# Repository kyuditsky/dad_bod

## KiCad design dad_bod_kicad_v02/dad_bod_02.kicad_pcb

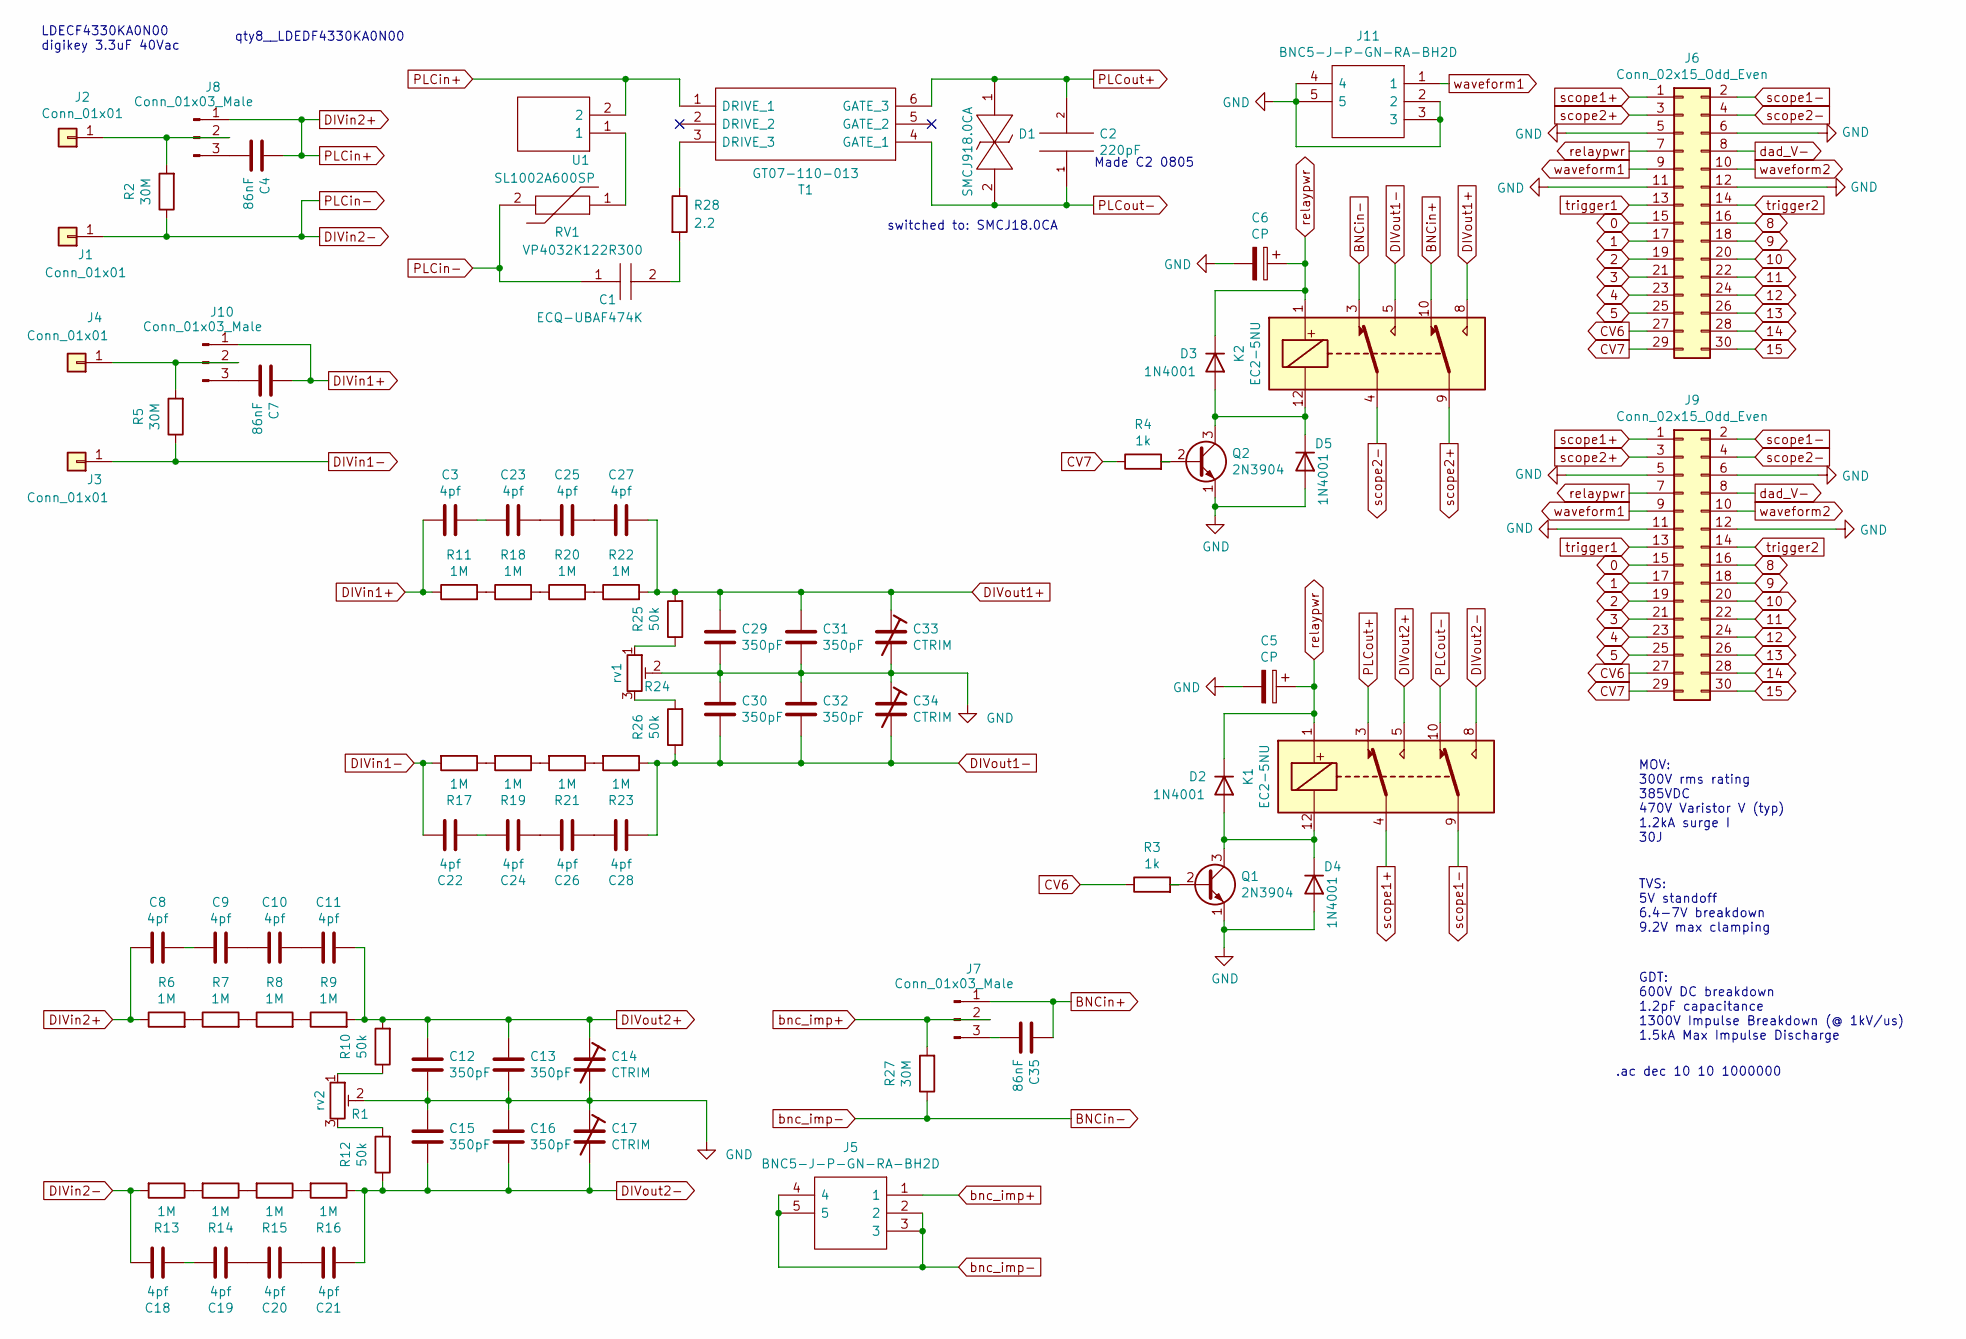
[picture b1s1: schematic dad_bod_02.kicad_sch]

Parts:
C1: ECQ-UBAF474K; ECQ-UBAF474K-3_side; Mouser Part Number 667-ECQ-UBAF474K
C2: 220pF; C_0603_1608Metric_Pad1.08x0.95mm_HandSolder
C3, C8, C9, C10, C11, C18, C19, C20, C21, C22, C23, C24, C25, C26, C27, C28: 4pf; C_0603_1608Metric_Pad1.08x0.95mm_HandSolder
C4, C7, C35: 86nF; C_0603_1608Metric_Pad1.08x0.95mm_HandSolder
C5, C6: CP; EEE1AA220WR
C12, C13, C15, C16, C29, C30, C31, C32: 350pF; C_0603_1608Metric_Pad1.08x0.95mm_HandSolder
C14, C17, C33, C34: CTRIM; C_Trimmer_Voltronics_JQ
D1: SMCJ918.0CA; DIONM7959X262N; Mouser Part Number 576-SMCJ9.0CA
D2, D3, D4, D5: 1N4001; D_DO-41_SOD81_P2.54mm_Vertical_KathodeUp
J1, J2, J3, J4: Conn_01x01; Banana_Jack_S_RA_73099
J5, J11: BNC5-J-P-GN-RA-BH2D; BNC5JPGNRABH2D; Mouser Part Number 200-BNC5JPGNRABH2D
J6: Conn_02x15_Odd_Even; PinHeader_2x15_P2.54mm_Horizontal
J7, J8, J10: Conn_01x03_Male; PinHeader_1x03_P2.54mm_Vertical
J9: Conn_02x15_Odd_Even
K1, K2: EC2-5NU; Relay_DPDT_Kemet_EC2
Q1, Q2: 2N3904; TO-92_Inline
R1: rv2; Potentiometer_Bourns_3314J_Vertical
R2, R5, R27: 30M; R_0603_1608Metric_Pad0.98x0.95mm_HandSolder
R3, R4: 1k; R_0603_1608Metric_Pad0.98x0.95mm_HandSolder
R6, R7, R8, R9, R11, R13, R14, R15, R16, R17, R18, R19, R20, R21, R22, R23: 1M; R_0603_1608Metric_Pad0.98x0.95mm_HandSolder
R10, R12, R25, R26: 50k; R_0603_1608Metric_Pad0.98x0.95mm_HandSolder
R24: rv1; Potentiometer_Bourns_3314J_Vertical
R28: 2.2; R_2010_5025Metric_Pad1.40x2.65mm_HandSolder
RV1: VP4032K122R300; CAPPM10080X500N; Mouser Part Number 80-VP4032K122R300
T1: GT07-110-013; GT07110013; Mouser Part Number 911-GT07-110-013
U1: SL1002A600SP; Mouser Part Number 576-SL1002A600SP

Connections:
0: J6.15, J9.15
1: J6.17, J9.17
2: J6.19, J9.19
3: J6.21, J9.21
4: J6.23, J9.23
5: J6.25, J9.25
8: J6.16, J9.16
9: J6.18, J9.18
10: J6.20, J9.20
11: J6.22, J9.22
12: J6.24, J9.24
13: J6.26, J9.26
14: J6.28, J9.28
15: J6.30, J9.30
BNCin+: C35.2, J7.1, K2.10
BNCin-: J5.2, J5.3, J5.4, J5.5, K2.3, R27.1
CV6: J6.27, J9.27, R3.1
CV7: J6.29, J9.29, R4.1
DIVin1+: C3.2, C7.2, J10.1, R11.1
DIVin1-: C22.1, J3.1, R5.1, R17.2
DIVin2+: C4.2, C8.2, J8.1, R6.1, T1.1 (DRIVE_1), U1.2
DIVin2-: C1.1, C18.1, J1.1, R2.1, R13.2, RV1.2
DIVout1+: C27.1, C29.2, C31.2, C33.1, K2.8, R22.2, R25.2
DIVout1-: C28.2, C30.1, C32.1, C34.2, K2.5, R23.1, R26.1
DIVout2+: C11.1, C12.2, C13.2, C14.1, K1.5, R9.2, R10.2
DIVout2-: C15.1, C16.1, C17.2, C21.2, K1.8, R12.1, R16.1
GND: C5.2, C6.2, C12.1, C13.1, C14.2, C15.2, C16.2, C17.1, C29.1, C30.2, C31.1, C32.2, C33.2, C34.1, D4.2 (A), D5.2 (A), J6.5, J6.6, J6.11, J6.12, J9.5, J9.6, J9.11, J9.12, J11.2, J11.3, J11.4, J11.5, Q1.1 (E), Q2.1 (E), R1.2, R24.2
unnamed: C1.2, R28.2
unnamed: C4.1, J8.3
unnamed: C7.1, J10.3
unnamed: C8.1, C9.2
unnamed: C10.1, C11.2
unnamed: C9.1, C10.2
unnamed: C18.2, C19.1
unnamed: C19.2, C20.1
unnamed: C20.2, C21.1
unnamed: C22.2, C24.1
unnamed: C23.1, C25.2
unnamed: C3.1, C23.2
unnamed: C24.2, C26.1
unnamed: C25.1, C27.2
unnamed: C26.2, C28.1
unnamed: C35.1, J7.3
unnamed: D2.2 (A), D4.1 (K), K1.12, Q1.3 (C)
unnamed: D3.2 (A), D5.1 (K), K2.12, Q2.3 (C)
unnamed: J2.1, J8.2, R2.2
unnamed: J4.1, J10.2, R5.2
unnamed: Q1.2 (B), R3.2
unnamed: Q2.2 (B), R4.2
unnamed: R1.1, R10.1
unnamed: R1.3, R12.2
unnamed: R6.2, R7.1
unnamed: R7.2, R8.1
unnamed: R8.2, R9.1
unnamed: R11.2, R18.1
unnamed: R13.1, R14.2
unnamed: R14.1, R15.2
unnamed: R15.1, R16.2
unnamed: R17.1, R19.2
unnamed: R18.2, R20.1
unnamed: R19.1, R21.2
unnamed: R20.2, R22.1
unnamed: R21.1, R23.2
unnamed: R24.1, R25.1
unnamed: R24.3, R26.2
unnamed: R28.1, T1.3 (DRIVE_3)
unnamed: RV1.1, U1.1
PLCout+: C2.2, D1.1, K1.3, T1.6 (GATE_3)
PLCout-: C2.1, D1.2, K1.10, T1.4 (GATE_1)
bnc_imp+: J5.1, J7.2, R27.2
dad_V-: J6.8, J9.8
relaypwr: C5.1, C6.1, D2.1 (K), D3.1 (K), J6.7, J9.7, K1.1, K2.1
scope1+: J6.1, J9.1, K1.4
scope1-: J6.2, J9.2, K1.9
scope2+: J6.3, J9.3, K2.9
scope2-: J6.4, J9.4, K2.4
trigger1: J6.13, J9.13
trigger2: J6.14, J9.14
waveform1: J6.9, J9.9, J11.1
waveform2: J6.10, J9.10

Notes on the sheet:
LDECF4330KA0N00 digikey 3.3uF 40Vac
Made C2 0805
TVS: 5V standoff 6.4-7V breakdown 9.2V max clamping
GDT: 600V DC breakdown 1.2pF capacitance 1300V Impulse Breakdown (@ 1kV/us) 1.5kA Max Impulse Discharge
qty8__LDEDF4330KA0N00
MOV: 300V rms rating 385VDC 470V Varistor V (typ) 1.2kA surge I 30J
.ac dec 10 10 1000000
switched to: SMCJ18.0CA

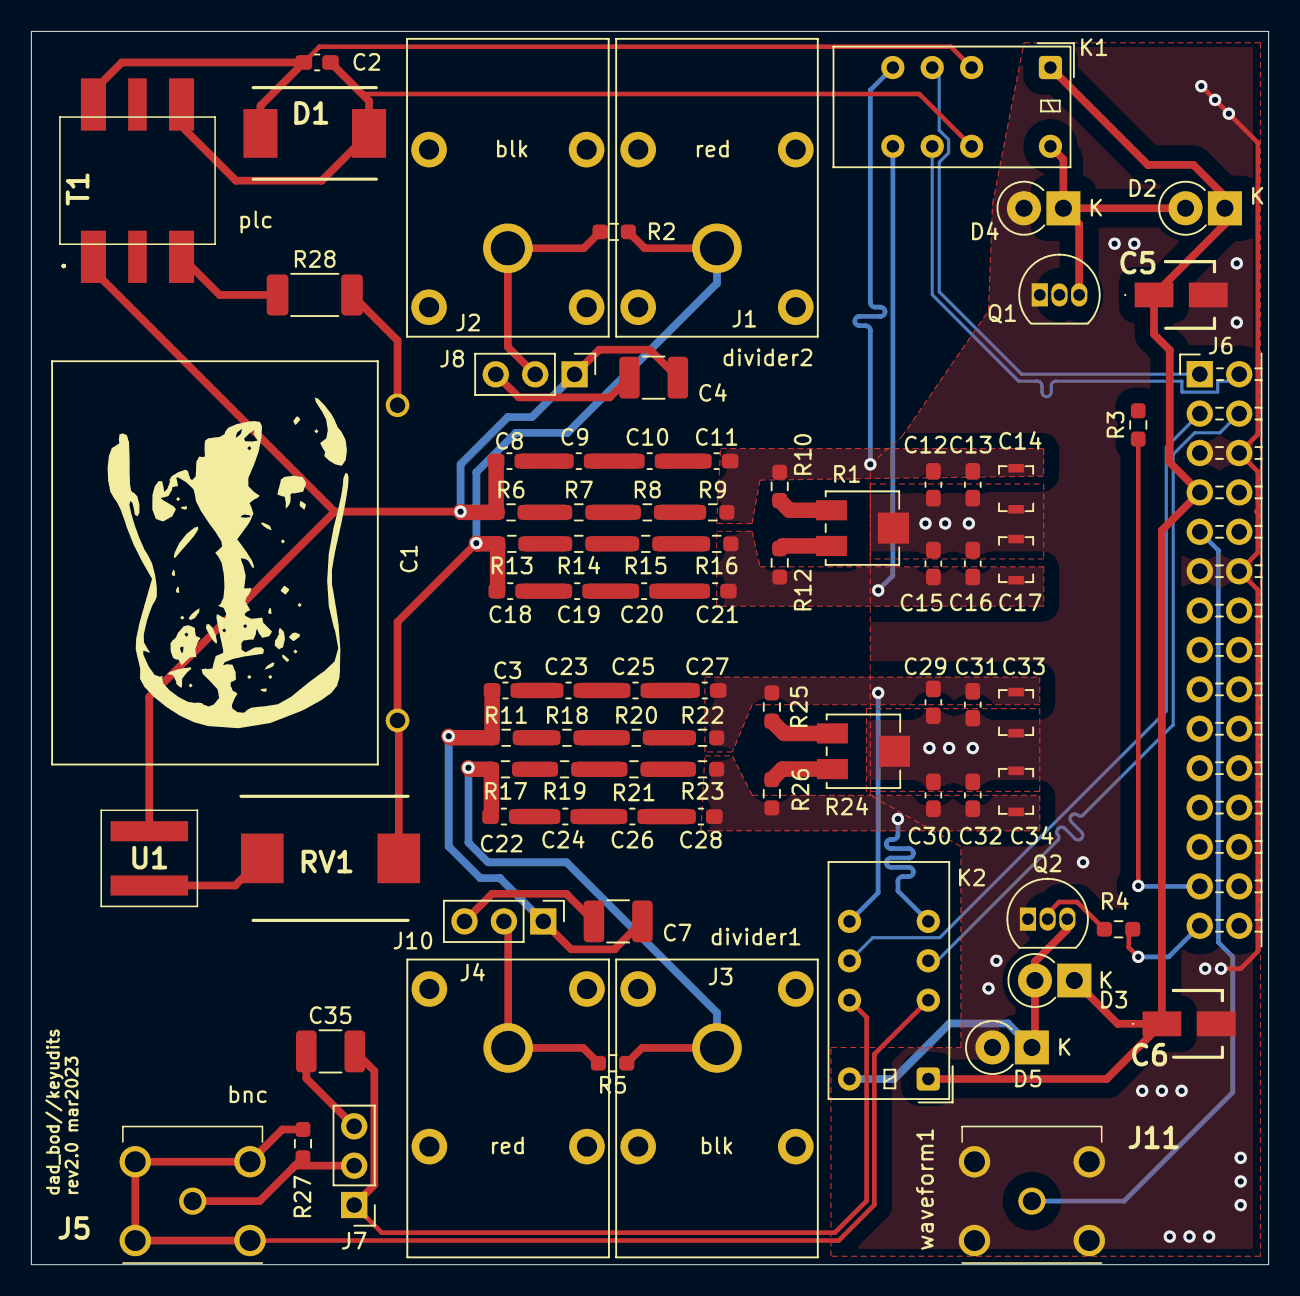
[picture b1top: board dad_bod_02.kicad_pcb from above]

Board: 2 copper layers, 79.8 x 79.5 mm, 85 parts (0 on the bottom side), 61 nets.

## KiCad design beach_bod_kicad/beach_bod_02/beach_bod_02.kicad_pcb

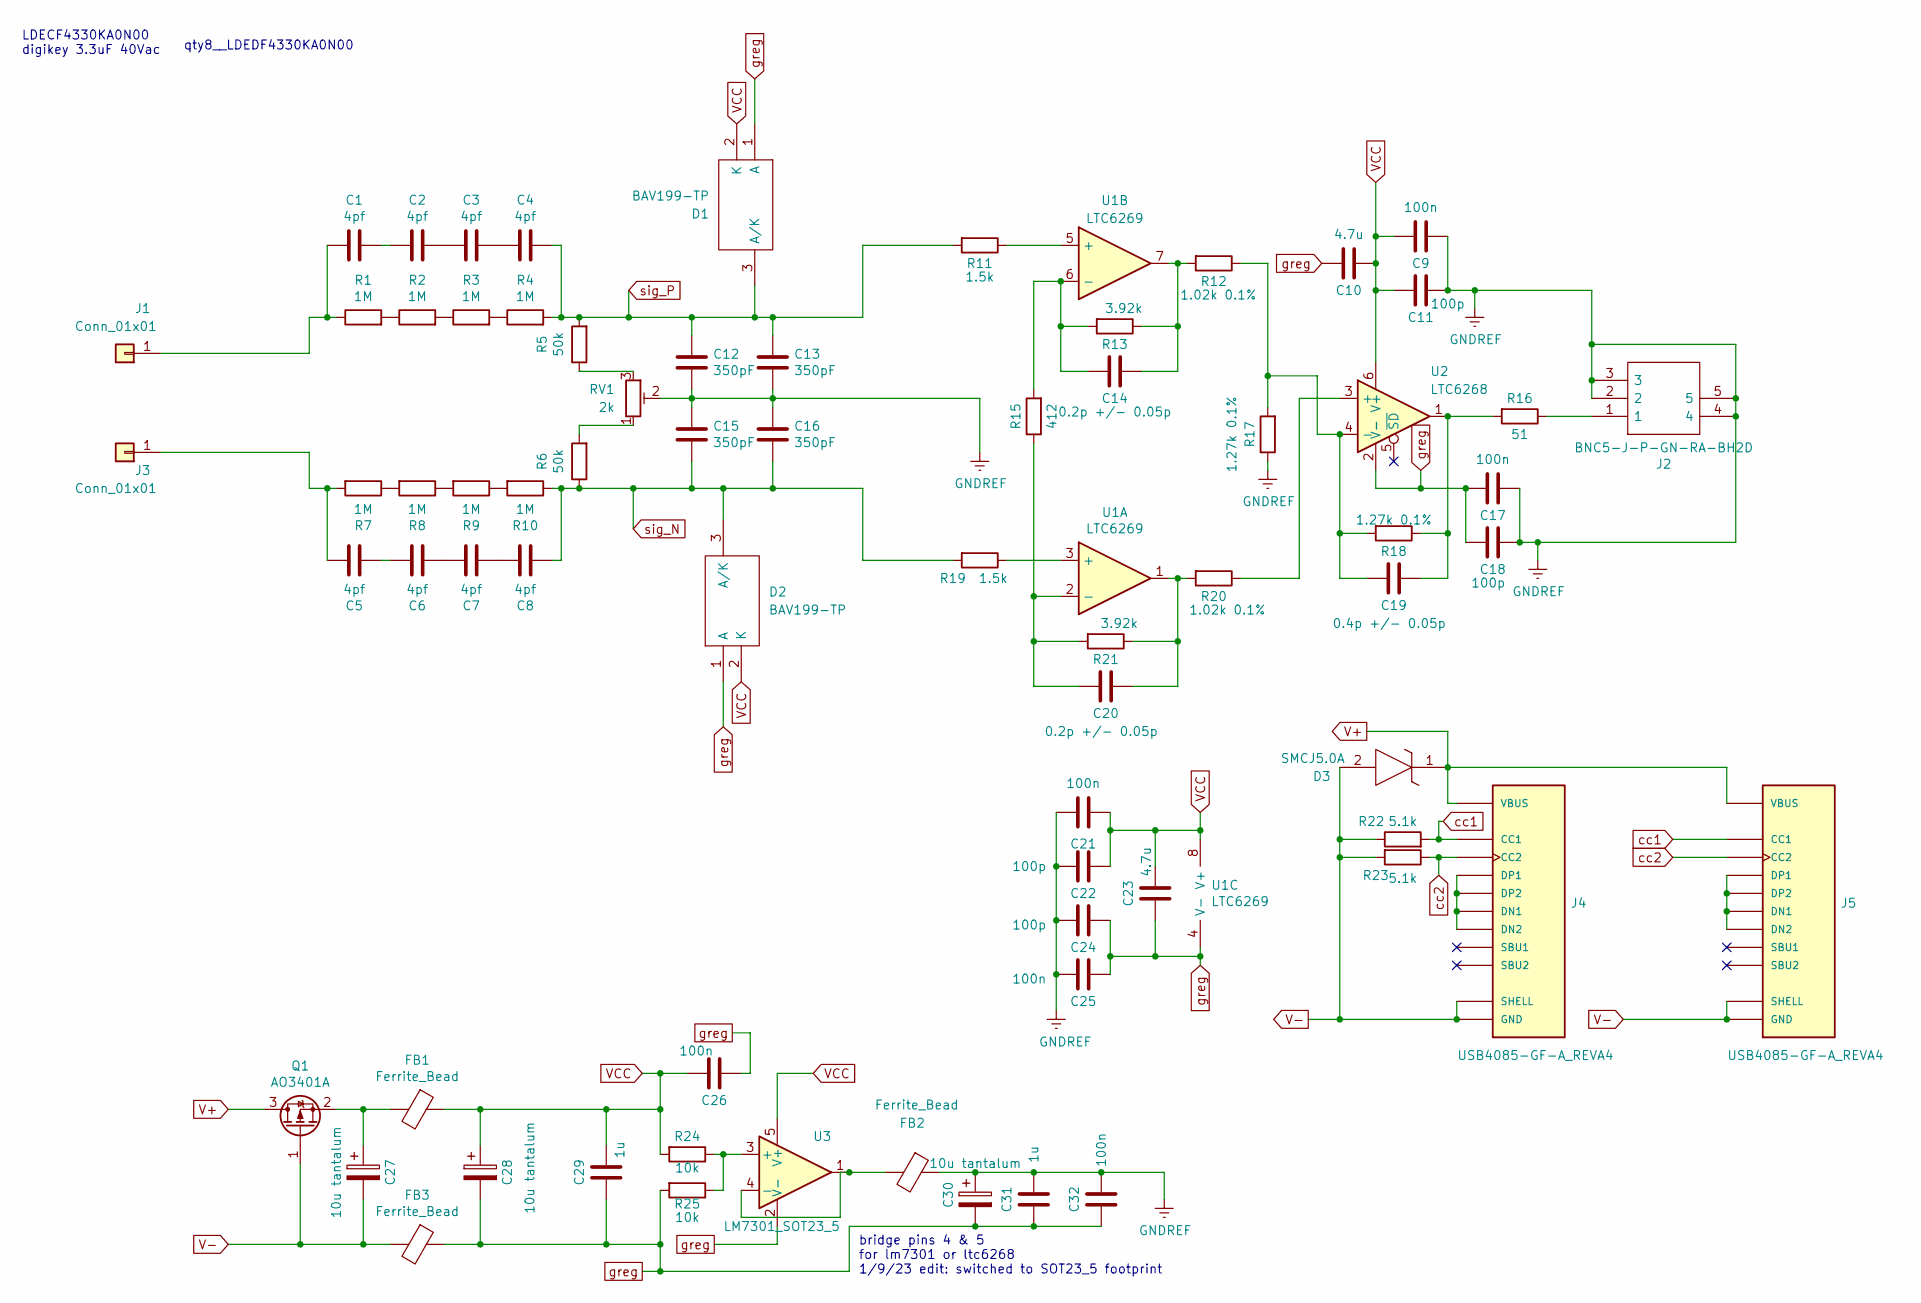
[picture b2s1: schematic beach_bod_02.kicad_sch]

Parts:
C1, C2, C3, C4, C5, C6, C7, C8: 4pf; C_0603_1608Metric_Pad1.08x0.95mm_HandSolder
C9, C17, C21, C25, C26, C32: 100n; C_0603_1608Metric_Pad1.08x0.95mm_HandSolder
C10, C23: 4.7u; C_0603_1608Metric_Pad1.08x0.95mm_HandSolder
C11, C18, C22, C24: 100p; C_0603_1608Metric_Pad1.08x0.95mm_HandSolder
C12, C13, C15, C16: 350pF; C_0603_1608Metric_Pad1.08x0.95mm_HandSolder
C14, C20: 0.2p +/- 0.05p; C_0603_1608Metric_Pad1.08x0.95mm_HandSolder
C19: 0.4p +/- 0.05p; C_0603_1608Metric_Pad1.08x0.95mm_HandSolder
C27, C28, C30: 10u tantalum; C_1210_3225Metric_Pad1.33x2.70mm_HandSolder
C29, C31: 1u; C_1210_3225Metric_Pad1.33x2.70mm_HandSolder
D1, D2: BAV199-TP; bav199_tp_SOT95P237X125-3N; Manufacturer_Part_Number BAV199-TP; Mouser Part Number 833-BAV199-TP
D3: SMCJ5.0A; littlefuseTVS; Mouser Part Number 576-SMCJ5.0A
FB1, FB2, FB3: Ferrite_Bead; R_0805_2012Metric_Pad1.20x1.40mm_HandSolder
J1, J3: Conn_01x01; Banana_Jack_S_RA_73099
J2: BNC5-J-P-GN-RA-BH2D; BNC5JPGNRABH2D; Mouser Part Number 200-BNC5JPGNRABH2D
J4, J5: USB4085-GF-A_REVA4; GCT_USB4085-GF-A_REVA4; PARTREV A4
Q1: AO3401A; SOT-23
R1, R2, R3, R4, R7, R8, R9, R10: 1M; R_0603_1608Metric_Pad0.98x0.95mm_HandSolder
R5, R6: 50k; R_0603_1608Metric_Pad0.98x0.95mm_HandSolder
R11, R19: 1.5k; R_0805_2012Metric_Pad1.20x1.40mm_HandSolder
R12, R20: 1.02k 0.1%; R_0805_2012Metric_Pad1.20x1.40mm_HandSolder
R13, R21: 3.92k; R_0805_2012Metric_Pad1.20x1.40mm_HandSolder
R15: 412; R_0805_2012Metric_Pad1.20x1.40mm_HandSolder
R16: 51; R_0805_2012Metric_Pad1.20x1.40mm_HandSolder
R17, R18: 1.27k 0.1%; R_0805_2012Metric_Pad1.20x1.40mm_HandSolder
R22, R23: 5.1k; R_0603_1608Metric_Pad0.98x0.95mm_HandSolder
R24, R25: 10k; R_0805_2012Metric_Pad1.20x1.40mm_HandSolder
RV1: 2k; Potentiometer_Bourns_3314J_Vertical
U1: LTC6269; SOP65P490X110-9N_LTC6269
U2: LTC6268; SOT95P280X100-6N_LTC6268
U3: LM7301_SOT23_5; SOT-23-5_HandSoldering

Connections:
GNDREF: C9.1, C11.1, C12.1, C13.1, C15.2, C16.2, C17.1, C18.1, C21.2, C22.2, C24.2, C25.2, C30.1, C31.2, C32.2, FB2.1, J2.2, J2.3, J2.4, J2.5, R17.1, RV1.2; also elsewhere on the board
unnamed: C1.1, C2.2
unnamed: C1.2, J1.1, R1.1
unnamed: C2.1, C3.2
unnamed: C3.1, C4.2
unnamed: C5.1, J3.1, R7.2
unnamed: C5.2, C6.1
unnamed: C6.2, C7.1
unnamed: C7.2, C8.1
unnamed: C14.1, R12.2, R13.1, U1.7
unnamed: C14.2, R13.2, R15.2, U1.6 (-)
unnamed: C19.1, R16.2, R18.1, U2.1
unnamed: C19.2, R12.1, R17.2, R18.2, U2.4 (-)
unnamed: C20.1, R20.2, R21.1, U1.1
unnamed: C20.2, R15.1, R21.2, U1.2 (-)
unnamed: C27.1, FB1.2, Q1.2 (S)
unnamed: FB2.2, U3.1, U3.4 (-)
unnamed: J2.1, R16.1
unnamed: J4.A6 (DP1), J4.A7 (DN1), J4.B6 (DP2), J4.B7 (DN2)
unnamed: J5.A6 (DP1), J5.A7 (DN1), J5.B6 (DP2), J5.B7 (DN2)
unnamed: R1.2, R2.1
unnamed: R2.2, R3.1
unnamed: R3.2, R4.1
unnamed: R5.1, RV1.3
unnamed: R6.2, RV1.1
unnamed: R7.1, R8.2
unnamed: R8.1, R9.2
unnamed: R9.1, R10.2
unnamed: R11.1, U1.5 (+)
unnamed: R19.1, U1.3 (+)
unnamed: R20.1, U2.3 (+)
unnamed: R24.1, R25.1, U3.3 (+)
V+: D3.1, J4.A4 (VBUS), J4.A9 (VBUS), J4.B4 (VBUS), J4.B9 (VBUS), J5.A4 (VBUS), J5.A9 (VBUS), J5.B4 (VBUS), J5.B9 (VBUS), Q1.3 (D)
V-: C27.2, D3.2, FB3.2, J4.A1 (GND), J4.A12 (GND), J4.B1 (GND), J4.B12 (GND), J4.P1 (SHELL), J4.P2 (SHELL), J4.P3 (SHELL), J4.P4 (SHELL), J5.A1 (GND), J5.A12 (GND), J5.B1 (GND), J5.B12 (GND), J5.P1 (SHELL), J5.P2 (SHELL), J5.P3 (SHELL), J5.P4 (SHELL), Q1.1 (G), R22.1, R23.2
VCC: C9.2, C10.1, C11.2, C21.1, C22.1, C23.2, C26.2, C28.1, C29.2, D1.2 (K), D2.2 (K), FB1.1, R24.2, U1.8 (V+), U2.6 (V+), U3.5 (V+); also elsewhere on the board
cc1: J4.A5 (CC1), J5.A5 (CC1), R22.2
cc2: J4.B5 (CC2), J5.B5 (CC2), R23.1
greg: C10.2, C17.2, C18.2, C23.1, C24.1, C25.1, C26.1, C28.2, C29.1, C30.2, C31.1, C32.1, D1.1 (A), D2.1 (A), FB3.1, R25.2, U1.4 (V-), U2.2 (V-), U3.2 (V-); also elsewhere on the board
sig_N: C8.2, C15.1, C16.1, D2.3 (A/K), R6.1, R10.1, R19.2; also elsewhere on the board
sig_P: C4.1, C12.2, C13.2, D1.3 (A/K), R4.2, R5.2, R11.2; also elsewhere on the board

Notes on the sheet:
LDECF4330KA0N00 digikey 3.3uF 40Vac
bridge pins 4 & 5 for lm7301 or ltc6268 1/9/23 edit: switched to SOT23_5 footprint
qty8__LDEDF4330KA0N00

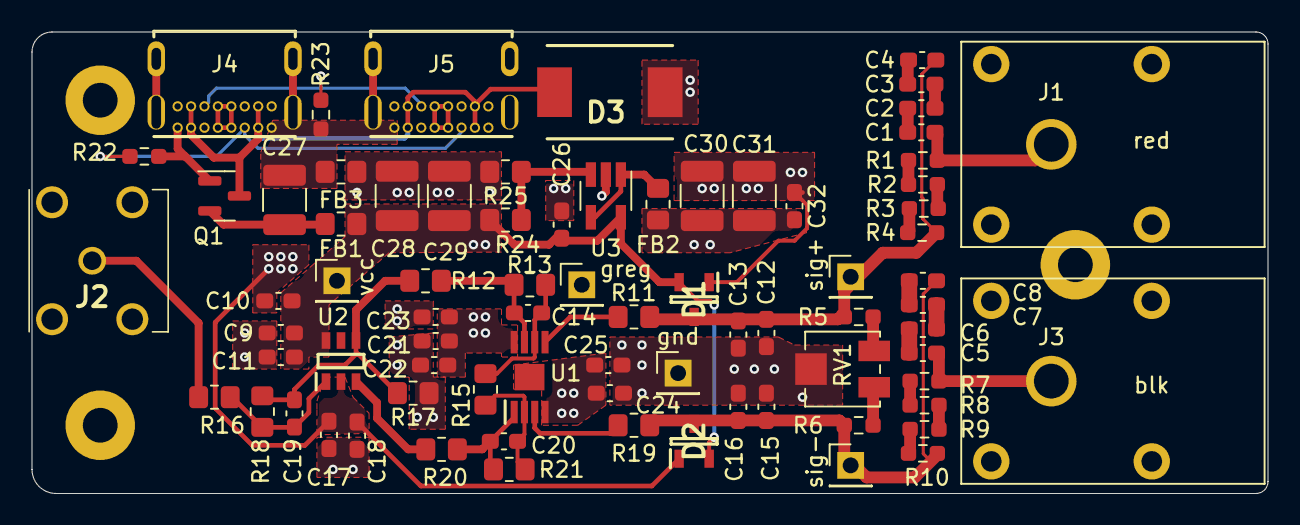
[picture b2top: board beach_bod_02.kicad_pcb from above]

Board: 2 copper layers, 78.2 x 29.2 mm, 77 parts (0 on the bottom side), 40 nets.

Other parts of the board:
gnd: PinHeader_1x01_P2.54mm_Vertical
greg: PinHeader_1x01_P2.54mm_Vertical
sig+: PinHeader_1x01_P2.54mm_Vertical
sig-: PinHeader_1x01_P2.54mm_Vertical
vcc: PinHeader_1x01_P2.54mm_Vertical

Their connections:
GNDREF: gnd.1; also elsewhere on the board
VCC: vcc.1; also elsewhere on the board
greg: greg.1; also elsewhere on the board
sig_N: sig-.1; also elsewhere on the board
sig_P: sig+.1; also elsewhere on the board

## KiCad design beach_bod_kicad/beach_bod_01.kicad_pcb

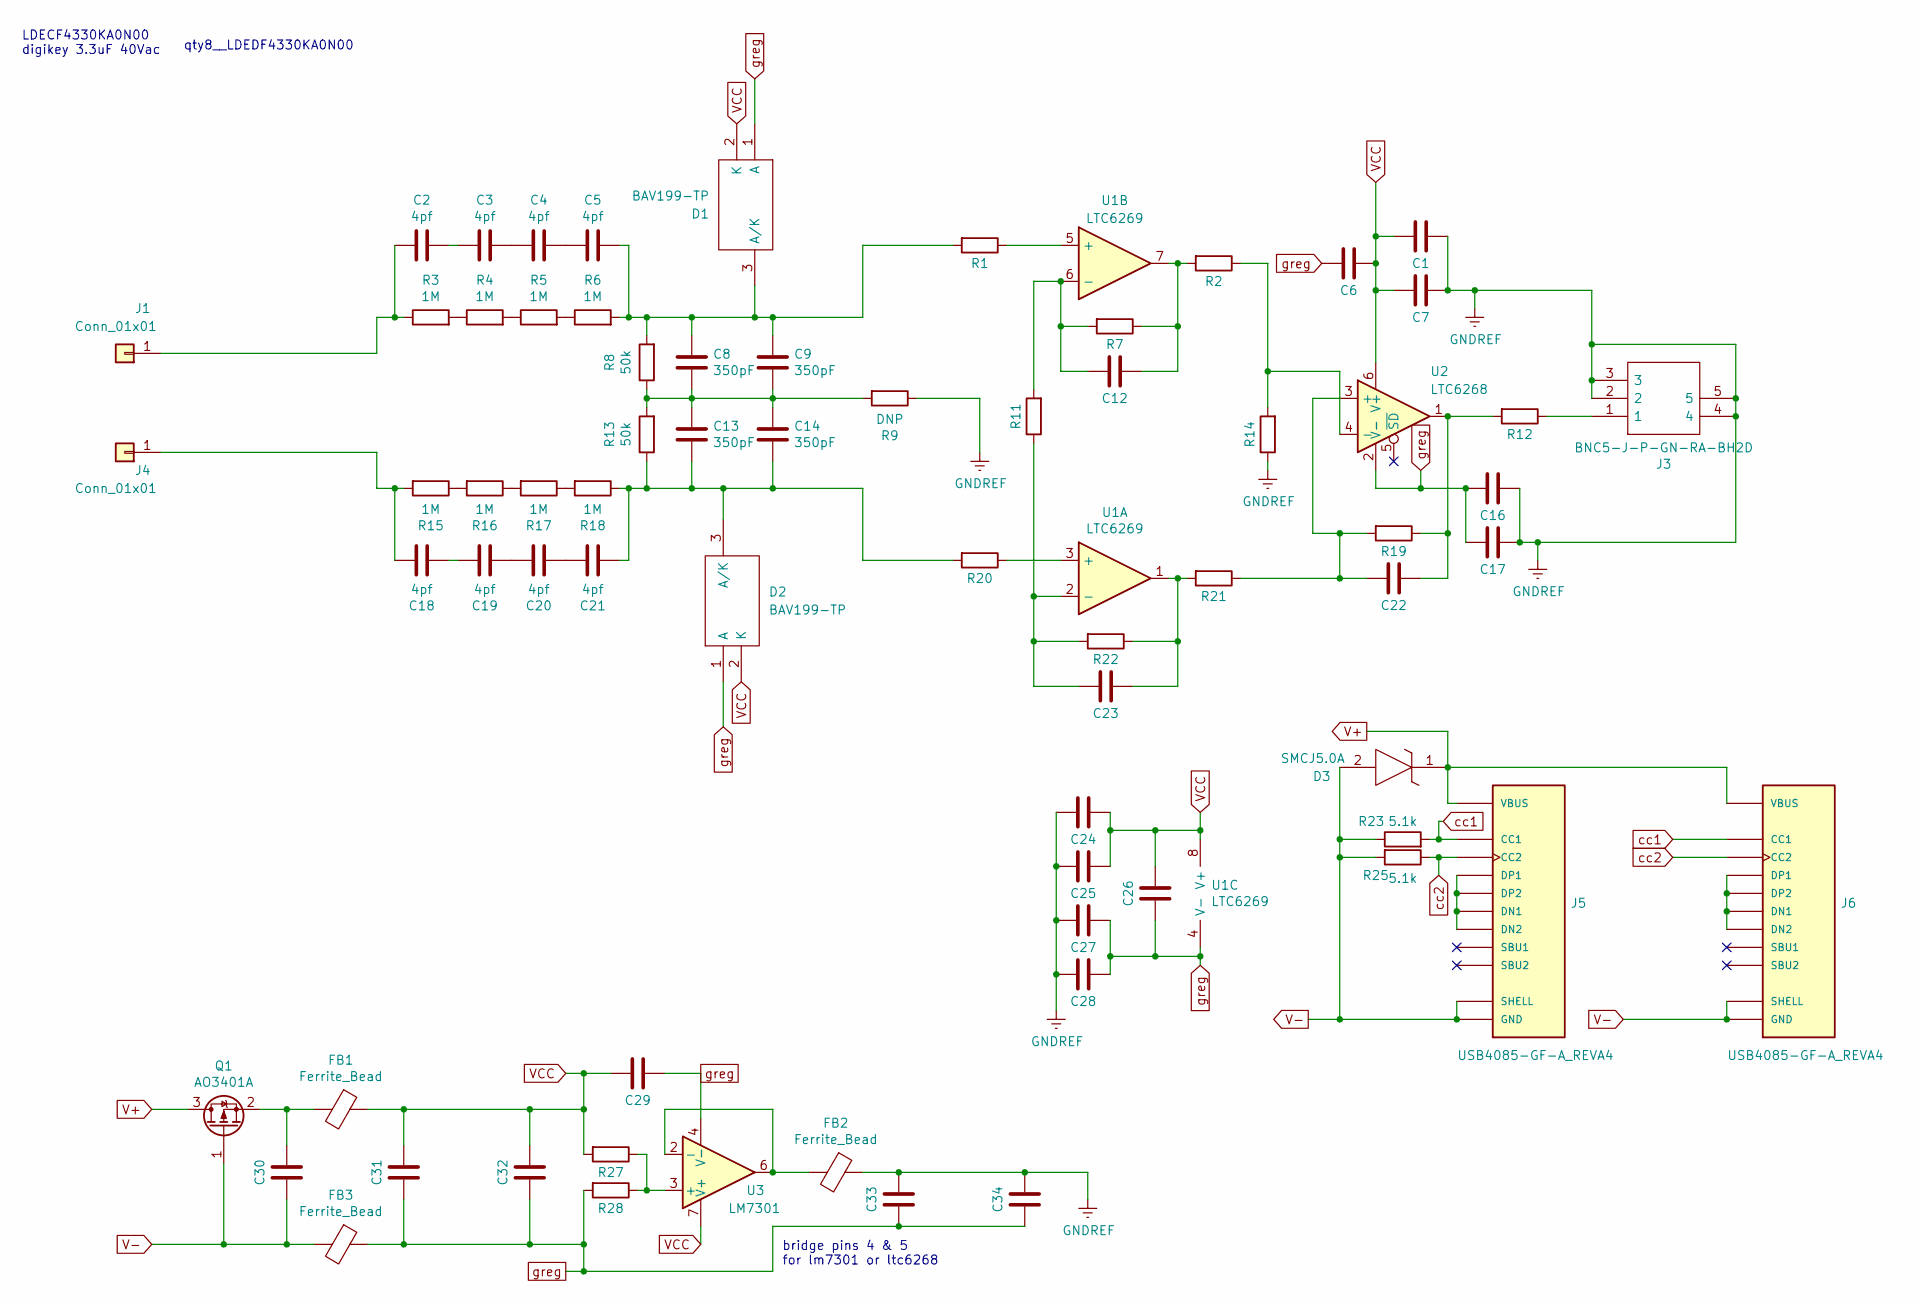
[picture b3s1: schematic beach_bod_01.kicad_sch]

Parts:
C1, C6, C7, C12, C16, C17, C22, C23, C24, C25, C26, C27, C28: C_0603_1608Metric_Pad1.08x0.95mm_HandSolder
C2, C3, C4, C5, C18, C19, C20, C21: 4pf; C_0805_2012Metric_Pad1.18x1.45mm_HandSolder
C8, C9, C13, C14: 350pF; C_0805_2012Metric_Pad1.18x1.45mm_HandSolder
C29: C_0805_2012Metric_Pad1.18x1.45mm_HandSolder
C30, C31, C32, C33, C34: C_1210_3225Metric_Pad1.33x2.70mm_HandSolder
D1, D2: BAV199-TP; bav199_tp_SOT95P237X125-3N; Manufacturer_Part_Number BAV199-TP; Mouser Part Number 833-BAV199-TP
D3: SMCJ5.0A; littlefuseTVS; Mouser Part Number 576-SMCJ5.0A
FB1, FB2, FB3: Ferrite_Bead; R_0805_2012Metric_Pad1.20x1.40mm_HandSolder
J1, J4: Conn_01x01; Banana_Jack_S_RA_73099
J3: BNC5-J-P-GN-RA-BH2D; BNC5JPGNRABH2D; Mouser Part Number 200-BNC5JPGNRABH2D
J5, J6: USB4085-GF-A_REVA4; GCT_USB4085-GF-A_REVA4; PARTREV A4
Q1: AO3401A; SOT-23
R1, R2, R7, R11, R12, R14, R19, R20, R21, R22, R27, R28: R_0805_2012Metric_Pad1.20x1.40mm_HandSolder
R3, R4, R5, R6, R15, R16, R17, R18: 1M; R_0805_2012Metric_Pad1.20x1.40mm_HandSolder
R8, R13: 50k; R_0805_2012Metric_Pad1.20x1.40mm_HandSolder
R9: DNP; R_0805_2012Metric_Pad1.20x1.40mm_HandSolder
R23, R25: 5.1k; R_0603_1608Metric_Pad0.98x0.95mm_HandSolder
U1: LTC6269; SOP65P490X110-9N_LTC6269
U2: LTC6268; SOT95P280X100-6N_LTC6268
U3: LM7301; SOIC127P600X175-8NLM7301

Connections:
GNDREF: C1.1, C7.1, C16.1, C17.1, C24.2, C25.2, C27.2, C28.2, C33.2, C34.2, FB2.1, J3.2, J3.3, J3.4, J3.5, R9.1, R14.1
unnamed: C2.1, C3.2
unnamed: C2.2, J1.1, R3.1
unnamed: C3.1, C4.2
unnamed: C4.1, C5.2
unnamed: C5.1, C8.2, C9.2, D1.3 (A/K), R1.2, R6.2, R8.2
unnamed: C12.1, R2.2, R7.1, U1.7
unnamed: C12.2, R7.2, R11.2, U1.6 (-)
unnamed 8: C13.1, C14.1, C21.2, D2.3 (A/K), R13.1, R18.1, R20.2; also elsewhere on the board
unnamed: C8.1, C9.1, C13.2, C14.2, R8.1, R9.2, R13.2
unnamed 10: C18.1, J4.1, R15.2; also elsewhere on the board
unnamed 11: C18.2, C19.1; also elsewhere on the board
unnamed 12: C19.2, C20.1; also elsewhere on the board
unnamed 13: C20.2, C21.1; also elsewhere on the board
unnamed: C22.1, R12.2, R19.1, U2.1
unnamed: C22.2, R19.2, R21.1, U2.3 (+)
unnamed: C23.1, R21.2, R22.1, U1.1
unnamed: C23.2, R11.1, R22.2, U1.2 (-)
unnamed: C30.2, FB1.2, Q1.2 (S)
unnamed: FB2.2, U3.2 (-), U3.6
unnamed: J3.1, R12.1
unnamed: J5.A6 (DP1), J5.A7 (DN1), J5.B6 (DP2), J5.B7 (DN2)
unnamed: J6.A6 (DP1), J6.A7 (DN1), J6.B6 (DP2), J6.B7 (DN2)
unnamed: R1.1, U1.5 (+)
unnamed: R3.2, R4.1
unnamed: R4.2, R5.1
unnamed: R5.2, R6.1
unnamed: R2.1, R14.2, U2.4 (-)
unnamed 28: R15.1, R16.2; also elsewhere on the board
unnamed 29: R16.1, R17.2; also elsewhere on the board
unnamed 30: R17.1, R18.2; also elsewhere on the board
unnamed: R27.1, R28.1, U3.3 (+)
unnamed: R20.1, U1.3 (+)
V+: D3.1, J5.A4 (VBUS), J5.A9 (VBUS), J5.B4 (VBUS), J5.B9 (VBUS), J6.A4 (VBUS), J6.A9 (VBUS), J6.B4 (VBUS), J6.B9 (VBUS), Q1.3 (D)
V-: C30.1, D3.2, FB3.2, J5.A1 (GND), J5.A12 (GND), J5.B1 (GND), J5.B12 (GND), J5.P1 (SHELL), J5.P2 (SHELL), J5.P3 (SHELL), J5.P4 (SHELL), J6.A1 (GND), J6.A12 (GND), J6.B1 (GND), J6.B12 (GND), J6.P1 (SHELL), J6.P2 (SHELL), J6.P3 (SHELL), J6.P4 (SHELL), Q1.1 (G), R23.1, R25.2
VCC: C1.2, C6.1, C7.2, C24.1, C25.1, C26.2, C29.2, C31.2, C32.2, D1.2 (K), D2.2 (K), FB1.1, R27.2, U1.8 (V+), U2.6 (V+), U3.7 (V+)
cc1: J5.A5 (CC1), J6.A5 (CC1), R23.2
cc2: J5.B5 (CC2), J6.B5 (CC2), R25.1
greg: C6.2, C16.2, C17.2, C26.1, C27.1, C28.1, C29.1, C31.1, C32.1, C33.1, C34.1, D1.1 (A), D2.1 (A), FB3.1, R28.2, U1.4 (V-), U2.2 (V-), U3.4 (V-)

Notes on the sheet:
LDECF4330KA0N00 digikey 3.3uF 40Vac
bridge pins 4 & 5 for lm7301 or ltc6268
qty8__LDEDF4330KA0N00

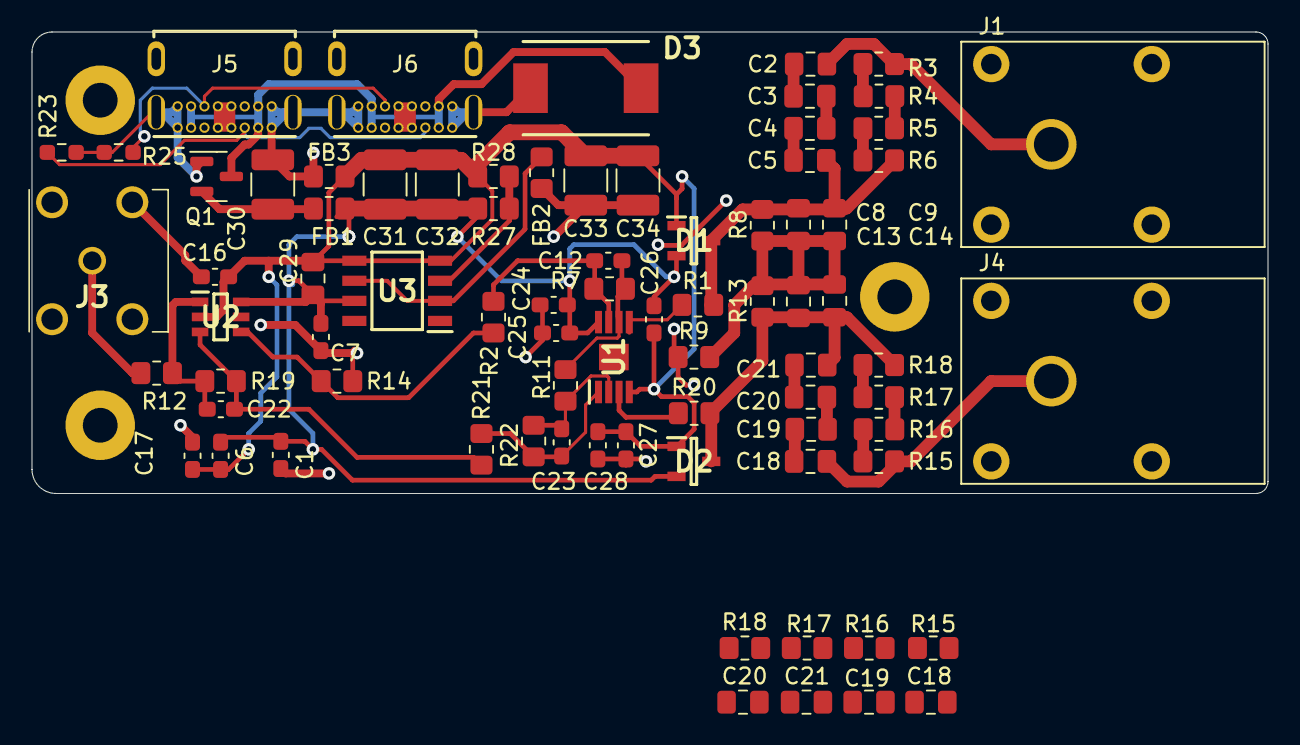
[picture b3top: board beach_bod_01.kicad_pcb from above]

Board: 2 copper layers, 78.2 x 29.2 mm, 79 parts (0 on the bottom side), 39 nets.

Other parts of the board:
C18#2, C19#2, C20#2, C21#2: 4pf; C_0805_2012Metric_Pad1.18x1.45mm_HandSolder
R15#2, R16#2, R17#2, R18#2: 1M; R_0805_2012Metric_Pad1.20x1.40mm_HandSolder

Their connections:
unnamed 8: C21#2.2, R18#2.1; also elsewhere on the board
unnamed 10: C18#2.1, R15#2.2; also elsewhere on the board
unnamed 11: C18#2.2, C19#2.1; also elsewhere on the board
unnamed 12: C19#2.2, C20#2.1; also elsewhere on the board
unnamed 13: C20#2.2, C21#2.1; also elsewhere on the board
unnamed 28: R15#2.1, R16#2.2; also elsewhere on the board
unnamed 29: R16#2.1, R17#2.2; also elsewhere on the board
unnamed 30: R17#2.1, R18#2.2; also elsewhere on the board
